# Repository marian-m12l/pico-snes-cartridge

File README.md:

# RP2350-based SNES cartridge

https://github.com/user-attachments/assets/8309a93a-a673-430d-9ed4-e411bfe92a66

## Pins

On rp2350 board (e.g. PGA2350):

- Address bus `A0`-`A23`: GPIO 0 (`A0`) to 23 (`A23`)
- Data bus `D0`-`D7`: GPIO 24 (`D0`) to 31 (`D7`)
- Cart pin `/CART`: GPIO 32
- Read pin `/RD`: GPIO 33
- Reset pin `/RESET`: GPIO 35
- CIC pin 24 `D1`: GPIO 37
- CIC pin 55 `D2`: GPIO 38
- CIC pin 56 `CLK`: GPIO 39
- CIC pin 25 `RST`: GPIO 40

- UART pins `TX` and `RX`: GPIO 44 and 45

## Build instructions

```
mkdir build
cd build
cmake -DPICO_SDK_PATH=/path/to/pico-sdk-2.1.0 -DPICO_BOARD=pimoroni_pga2350 ..
make
```

# Adding ROMs

Add `rom.sfc` in slot `1`:
```
./tools/loadrom.sh rom.sfc 1"
```

Each slot (from 1 to 15) occupies 1MiB in flash memory.

# Running

```
$ openocd-rpi/installed/bin/openocd -f interface/jlink.cfg -c "transport select swd" -c "adapter speed 6000" -f target/rp2350.cfg
$ arm-none-eabi-gdb -ex 'target remote localhost:3333' -ex 'load' -ex 'monitor reset init' -ex 'continue' pico-snes-cartridge.elf
$ picocom -b 115200 /dev/ttyACM0 -g picocom.log
```

# Reset behaviour

Once you've selected a game, pressing the reset button on the SNES will restart this game.

A long-press (~1 second) will go back to the launcher.

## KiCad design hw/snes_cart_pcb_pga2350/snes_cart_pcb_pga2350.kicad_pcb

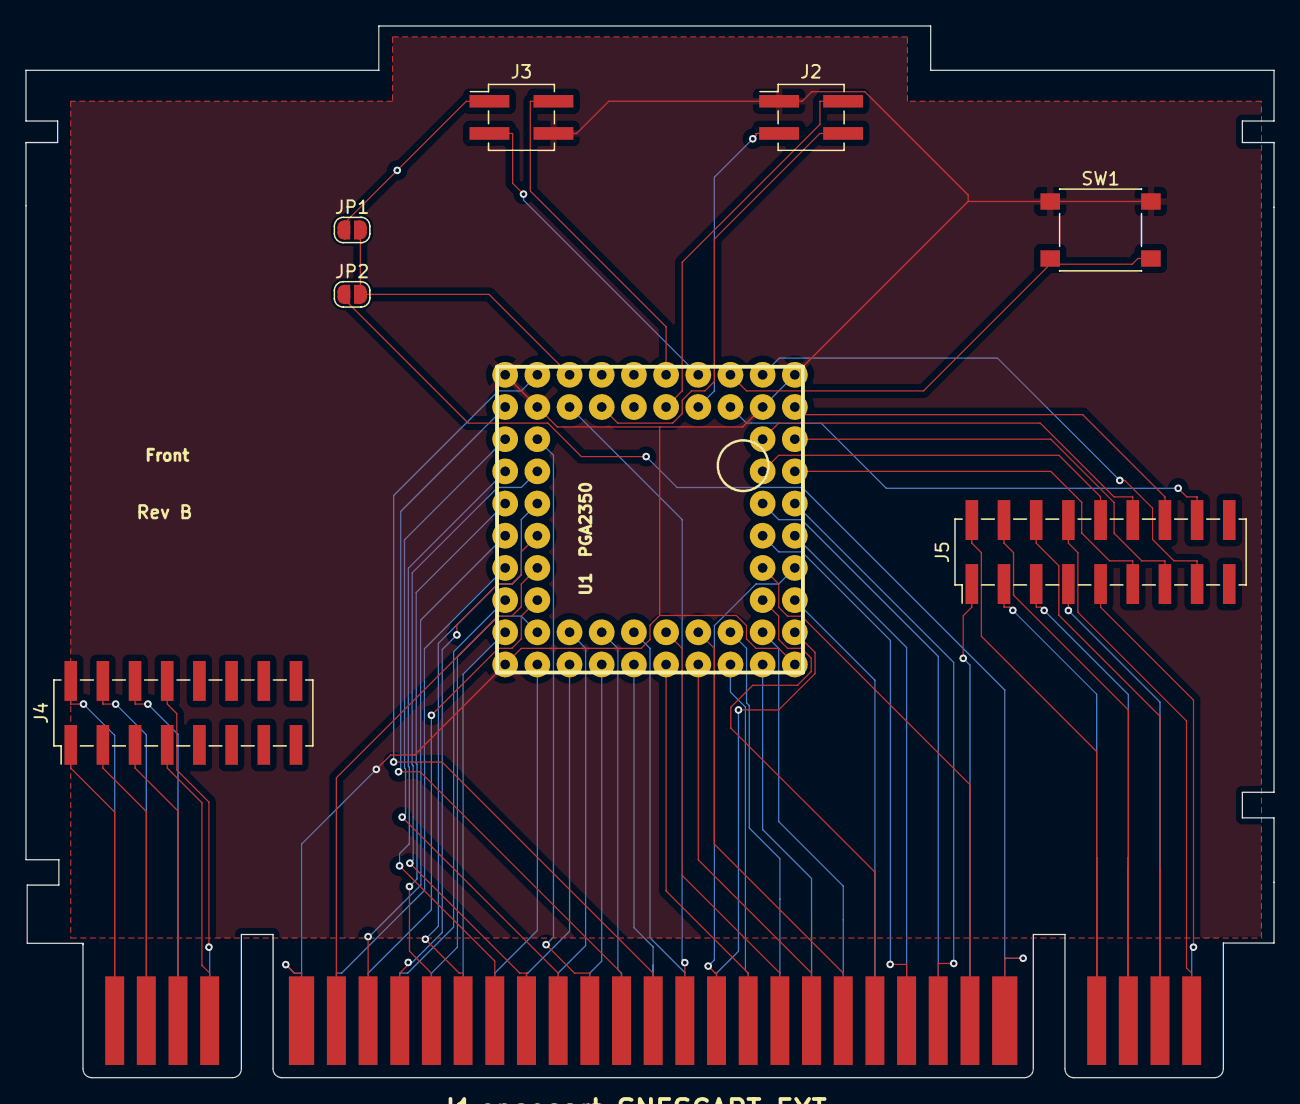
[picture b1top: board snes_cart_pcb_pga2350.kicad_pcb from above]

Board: 2 copper layers, 98.5 x 83.0 mm, 9 parts (0 on the bottom side), 75 nets.

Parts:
J1: snescart_SNESCART_EXT; SNESCART_EXT_100mm
J2, J3: Conn_02x02_Counter_Clockwise; PinHeader_2x02_P2.54mm_Vertical_SMD
J4: Conn_02x08_Counter_Clockwise; PinHeader_2x08_P2.54mm_Vertical_SMD
J5: Conn_02x09_Counter_Clockwise; PinHeader_2x09_P2.54mm_Vertical_SMD
JP1, JP2: SolderJumper_2_Open; SolderJumper-2_P1.3mm_Open_RoundedPad1.0x1.5mm
SW1: SW_Push; SW_Push_1P1T_NO_6x6mm_H9.5mm
U1: PGA2350

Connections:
/3V3: J2.4, U1.B4 (PIN)
/A0: J1.17 (A0), U1.B3 (PIN)
/A1: J1.16 (A1), U1.A2 (PIN)
/A2: J1.15 (A2), U1.B1 (PIN)
/A3: J1.14 (A3), U1.C2 (PIN)
/A4: J1.13 (A4), U1.C1 (PIN)
/A5: J1.12 (A5), U1.D2 (PIN)
/A6: J1.11 (A6), U1.D1 (PIN)
/A7: J1.10 (A7), U1.E2 (PIN)
/A8: J1.9 (A8), U1.E1 (PIN)
/A9: J1.8 (A9), U1.F2 (PIN)
/A10: J1.7 (A10), U1.F1 (PIN)
/A11: J1.6 (A11), U1.G2 (PIN)
/A12: J1.37 (A12), U1.G1 (PIN)
/A13: J1.38 (A13), U1.H2 (PIN)
/A14: J1.39 (A14), U1.H1 (PIN)
/A15: J1.40 (A15), U1.J2 (PIN)
/A16: J1.41 (A16), U1.J1 (PIN)
/A17: J1.42 (A17), U1.K2 (PIN)
/A18: J1.43 (A18), U1.K3 (PIN)
/A19: J1.44 (A19), U1.J3 (PIN)
/A20: J1.45 (A20), U1.K4 (PIN)
/A21: J1.46 (A21), U1.J4 (PIN)
/A22: J1.47 (A22), U1.K5 (PIN)
/A23: J1.48 (A23), U1.J5 (PIN)
/BOOTSEL: SW1.2, U1.A8 (PIN)
/CIC_P1_DOUT: J1.24 (CIC_P1_DOUT), U1.F9 (PIN)
/CIC_P2_DIN: J1.55 (CIC_P2_DIN), U1.F10 (PIN)
/CIC_P6_CLK: J1.56 (CIC_P6_CLK), U1.E9 (PIN)
/CIC_P7_RESET: J1.25 (CIC_P7_RESET), U1.E10 (PIN)
/CPU_CLK: J1.57 (CPU_CLK), J5.1
/D0: J1.19 (D0), U1.K6 (PIN)
/D1: J1.20 (D1), U1.J6 (PIN)
/D2: J1.21 (D2), U1.K7 (PIN)
/D3: J1.22 (D3), U1.J7 (PIN)
/D4: J1.50 (D4), U1.K8 (PIN)
/D5: J1.51 (D5), U1.J8 (PIN)
/D6: J1.52 (D6), U1.K9 (PIN)
/D7: J1.53 (D7), U1.J9 (PIN)
/EXPAND: J1.2 (EXPAND), J4.3
/GND: J1.5 (GND), J1.36 (GND), J2.1, J3.4, SW1.1, U1.A1 (PIN), U1.A10 (PIN), U1.B2 (PIN), U1.B9 (PIN), U1.K1 (PIN), U1.K10 (PIN)
/GP41: J5.10, U1.D9 (PIN)
/GP42: J5.11, U1.D10 (PIN)
/GP43: J5.12, U1.C9 (PIN)
/GP44: J5.13, U1.C10 (PIN)
/GP45: J5.14, U1.B10 (PIN)
/GP46: J5.15, U1.A9 (PIN)
/GP47: J5.16, U1.B8 (PIN)
/LINE_L: J1.31 (LINE_L), J5.8
/LINE_R: J1.62 (LINE_R), J5.9
/PA0: J1.28 (PA0), J5.2
/PA1: J1.59 (PA1), J5.3
/PA2: J1.29 (PA2), J5.4
/PA3: J1.60 (PA3), J5.5
/PA4: J1.30 (PA4), J5.6
/PA5: J1.61 (PA5), J5.7
/PA6: J1.3 (PA6), J4.5
/PA7: J1.34 (PA7), J4.6
/REFRESH: J1.33 (REFRESH), J4.4
/SWCLK: J2.2, U1.B6 (PIN)
/SWDIO: J2.3, U1.B7 (PIN)
/SYS_CLK: J1.1 (SYS_CLK), J4.1
/USB_DM: J3.3, U1.A7 (PIN)
/USB_DP: J3.2, U1.A6 (PIN)
/USB_VBUS: J3.1, JP1.1 (A)
/VBUS: JP1.2 (B), JP2.2 (B), U1.A3 (PIN)
/VCC: J1.27 (VCC), J1.58 (VCC), JP2.1 (A)
//IRQ: J1.18 (/IRQ), U1.G10 (PIN)
//PARD: J1.4 (/PARD), J4.7
//PAWR: J1.35 (/PAWR), J4.8
//RD: J1.23 (/RD), U1.H9 (PIN)
//RESET: J1.26 (/RESET), U1.G9 (PIN)
//ROMSEL: J1.49 (/ROMSEL), U1.J10 (PIN)
//WR: J1.54 (/WR), U1.H10 (PIN)
//WRAM: J1.32 (/WRAM), J4.2

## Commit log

2024-08-09 first signs of life
2024-08-09 add pinout
2024-08-09 pinout
2024-08-12 move roms data
2024-08-14 use rp2350 + add support for bank address
2024-08-14 fix overclocking
2024-08-15 check romtype at boot time + add test roms
2024-08-15 add rom
2024-08-15 log repeated reads
2025-01-04 (wip) erratum e9 workaround for pin 12
2025-01-05 add pcb design
2025-01-08 fix pins
2025-01-18 works on pcb rev1
2025-02-13 (wip) initial support for cic on core1
2025-02-19 (wip) banked 512KiB rom in ram (incl. pinned cache lines and usb dpram) + some more mess
2025-02-19 multiple ram load modes
2025-02-19 force lorom for fastrom
2025-02-19 add homebrews
2025-03-07 fix header detection + fix hirom mapping + run rom with cic code enabled (wip)
2025-03-09 refactor
2025-03-09 wip sram support
2025-03-09 clean roms
2025-03-09 gitignore
2025-03-11 fix romsize type...
2025-03-11 missing include
2025-03-11 sram support for hirom (untested)
2025-03-11 fix hirom
2025-03-11 cic breaks large roms?
2025-04-15 add menu
2025-04-15 document how to add rom
2025-04-15 add tool to load roms
2025-04-15 fix rom names
2025-04-17 tool lists slots
2025-04-17 selected rom zero-initialized + readme
2025-04-22 rename launcher + cleanup
2025-06-20 flaky reset-to-launcher feature
2025-06-20 disable reset to launcher
2025-06-23 fix reset-to-launcher with long-press of reset button
2025-06-23 document reset to launcher
2025-06-23 fix loadrom tool
2025-10-10 fix loadrom.sh
2025-10-30 Update README.md add board pictures
